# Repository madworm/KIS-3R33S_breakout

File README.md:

KIS-3R33S_breakout
==================

LAYOUT FILES: - see title -

---

Before having PC-boards made, please make sure you know about your manufacturer's peculiarities!
Especially drill-sizes and their tolerances may vary too much and give you trouble.

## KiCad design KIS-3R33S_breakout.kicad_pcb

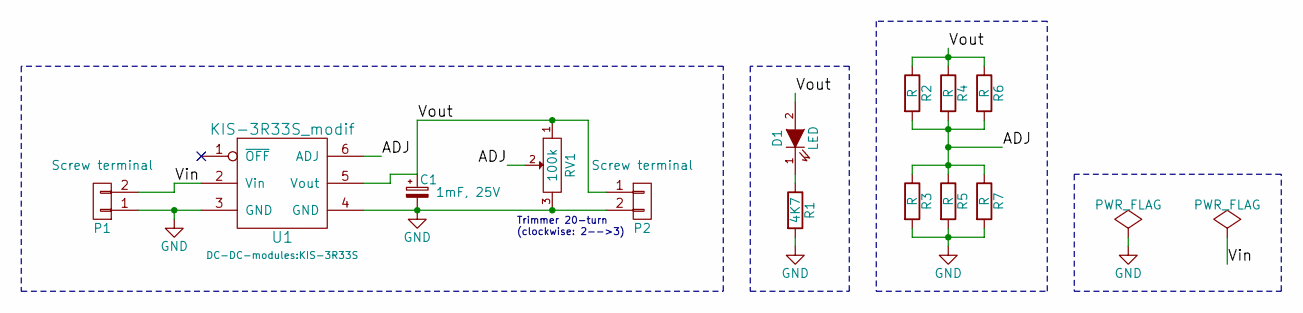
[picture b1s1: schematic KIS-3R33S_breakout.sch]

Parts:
C1: 1mF, 25V; c_elec_SMD_12.5x13.5
D1: LED; LED-0805
P1, P2: Screw terminal; MADW__SCREW_TERMINAL_2pin
R1: 4K7; R_0603_HandSoldering
R2, R3, R4, R5, R6, R7: R; R_0603_HandSoldering
RV1: 100k; trimmer-pot_side-adjust_TSR-3006P_TH
U1: KIS-3R33S_modif; KIS-3R33S

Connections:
/ADJ: R2.2, R3.1, R4.2, R5.1, R6.2, R7.1, RV1.2, U1.6 (ADJ)
/Vin: P1.2, U1.2 (Vin)
/Vout: C1.1, D1.2 (A), P2.1, R2.1, R4.1, R6.1, RV1.1, U1.5 (Vout)
GND: C1.2, P1.1, P2.2, R1.2, R3.2, R5.2, R7.2, RV1.3, U1.3 (GND), U1.4 (GND)
unnamed: D1.1 (K), R1.1

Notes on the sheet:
Trimmer 20-turn (clockwise: 2-->3)

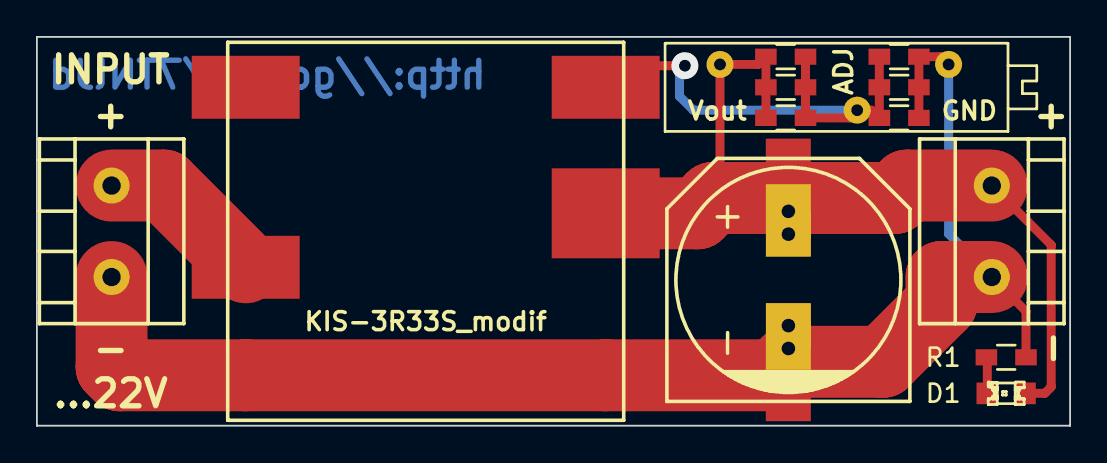
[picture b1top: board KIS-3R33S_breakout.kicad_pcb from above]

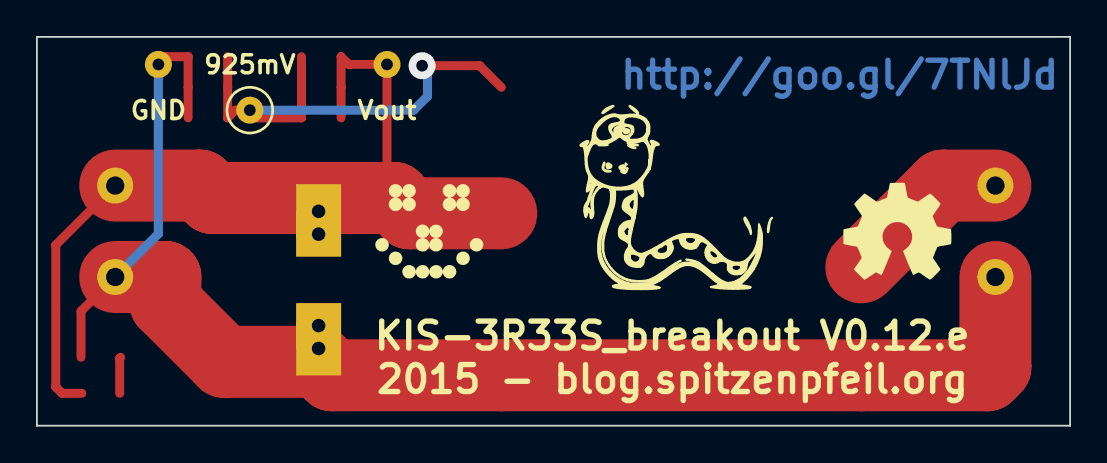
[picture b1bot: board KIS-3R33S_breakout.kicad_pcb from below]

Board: 2 copper layers, 57.4 x 21.6 mm, 15 parts (2 on the bottom side), 5 nets.

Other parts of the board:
LOGO1: LED_smile_silkscreen_6mm
LOGO2: OSHW-logo_silkscreen_6mm

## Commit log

2015-05-02 Added 'Docs'.
2015-05-02 First doodles.
2015-05-02 Throwing parts around.
2015-05-02 Done?
2015-05-02 Board-shrink.
2015-05-03 Added optional descrete resistive-divider.
2015-05-03 Adjustment pot was reversed. Vout should go up turning clockwise.
2015-05-03 Board shrink.
2015-05-03 Silkscreen tweaks.
2015-05-03 Added comment to schematic.
2015-05-03 Added 'Snake' to silkscreen.
2015-07-22 Added note regarding necessary removal of D2.
2015-07-22 Updated 'readme.txt'.
2015-07-23 Tweaked SMD capacitor footprint (added thermal vias / TH pads).
2015-07-23 Fixed missing '('. Must have been wrecked in previous commit.
2015-09-07 Fixed wrong net & pad number for big cap (added TH pads).
